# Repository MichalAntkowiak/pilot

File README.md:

# Pilot IR na ATtiny1614

Pilot na podczerwień do telewizora, zaprojektowany od zera w KiCadzie: od policzenia wartości elementów, przez schemat, po samodzielnie poprowadzoną dwuwarstwową płytkę drukowaną. Zasilany z dwóch baterii AAA, ma sześć przycisków i diodę IR sterowaną przez tranzystor.

**Status:** projekt PCB ukończony (ERC, DRC i zgodność ze schematem bez błędów), firmware w przygotowaniu.

## Założenia projektu

**Pilot nadający.** Kody komend telewizora są zapisane w firmware, a naciśnięcie przycisku wysyła gotową komendę. Wariant „uczący się”, z odbiornikiem IR do nagrywania oryginalnego pilota, zostawiłem na wersję drugą. Tor nadawczy jest w obu wersjach identyczny, więc najpierw warto go opanować.

**Zasilanie z 2 × AAA, bez włącznika.** ATtiny1614 pracuje bezpośrednio z baterii (od 1,8 V), a w uśpieniu pobiera ułamek mikroampera, więc wyłącznik nie jest potrzebny. Mikrokontroler budzi naciśnięcie przycisku.

**Mikrokontroler dobrany pod baterie.** Rozważałem znany mi już ESP32-C3, ale potrzebuje on stabilizowanych 3,3 V (dwie baterie AAA dają 3 V i mniej) i pobiera znacznie więcej prądu. Wymagałby przetwornicy na płytce i szybciej rozładowywałby baterie. ATtiny upraszcza schemat kosztem nowego toolchainu: megaTinyCore w Arduino IDE i programowanie przez UPDI.

**Sześć przycisków:** zasilanie, głośność +/−, kanał +/− i wyciszenie.

**Nośna 38 kHz generowana sprzętowo** przez timer TCA0 na pinie PB0, więc jej przebieg nie zależy od tego, co w danej chwili robi program.

## Schemat

Schemat składa się z czterech bloków.

**Zasilanie.** Koszyk BT1 zasila sieć VCC, a kondensator C1 (100 nF) odsprzęga ATtiny.

**Przyciski.** Każdy zwiera swój pin do masy. Rezystory podciągające są wbudowane w ATtiny i włączane programowo, więc na płytce ich nie ma. Połączenia prowadzą etykiety sieci, dzięki czemu schemat pozostaje czytelny.

**Tor nadawczy.** Pin PB0 (etykieta `IR_OUT`) przez R1 steruje bazą tranzystora Q1, który przełącza obwód VCC → R2 → D1 → Q1 → GND. Kondensator C2 (22 µF) przy diodzie pokrywa impulsy prądu.

**Programowanie.** Złącze J1 wyprowadza UPDI (PA0), VCC i GND.

## Obliczenia

Wartości elementów toru nadawczego policzyłem sam, a potem dobrałem najbliższe wartości z typoszeregu.

**R2: ograniczenie prądu diody IR (cel: 100 mA)**

```
R2 = (U_bat − U_D − U_CE(sat)) / I_D
   = (3,0 V − 1,3 V − 0,3 V) / 0,1 A = 14 Ω   →   15 Ω  (I_D ≈ 93 mA)
```

Zaokrąglenie w górę: nieco mniejszy prąd, więc założenie nie zostaje przekroczone.

**R1: rezystor bazy Q1**

```
I_B ≈ I_C / 10 = 93 mA / 10 = 9,3 mA
R1  = (U_PB0 − U_BE) / I_B = (3,0 V − 0,8 V) / 9,3 mA ≈ 236,6 Ω   →   220 Ω  (I_B ≈ 10 mA)
```

Zaokrąglenie w dół: większy prąd bazy daje pewniejsze nasycenie tranzystora.

**C2: zbiornik na impulsy diody**

```
C = I · t / ΔV = 0,093 A · 9 µs / 0,1 V ≈ 8,4 µF   →   22 µF
```

t to czas jednego błysku przy nośnej 38 kHz, a ΔV to dopuszczalny spadek napięcia. Najbliższa wartość to 10 µF, ale ceramiczne kondensatory tracą pojemność pod napięciem i 10 µF przy 3 V realnie ma około 7 µF. Stąd 22 µF w obudowie 1206.

## Komponenty

| Oznaczenie | Element | Obudowa | Rola |
|---|---|---|---|
| U1 | ATtiny1614 | SOIC-14 | mikrokontroler |
| D1 | dioda IR 940 nm | 5 mm, montaż poziomy | nadajnik podczerwieni |
| Q1 | tranzystor NPN 2N3904 | TO-92 | przełącznik diody |
| R1 | rezystor 220 Ω | 0805 | rezystor bazy Q1 |
| R2 | rezystor 15 Ω | 0805 | ograniczenie prądu diody |
| C1 | kondensator ceramiczny 100 nF | 0805 | odsprzęganie U1 |
| C2 | kondensator ceramiczny 22 µF | 1206 | zbiornik na impulsy diody |
| SW1–SW6 | przycisk tact switch | 6 × 6 mm, THT | przyciski pilota |
| BT1 | koszyk 2 × AAA | Keystone 2468 | zasilanie, spód płytki |
| J1 | listwa goldpin 1 × 3 | raster 2,54 mm | programowanie UPDI |

## Przypisanie pinów

| Pin ATtiny1614 | Sieć | Funkcja |
|---|---|---|
| PA0 (10) | UPDI | programowanie |
| PA1 (11) | power | włącz / wyłącz |
| PA2 (12) | vol+ | głośniej |
| PA3 (13) | vol− | ciszej |
| PA4 (2) | ch+ | następny kanał |
| PA5 (3) | ch− | poprzedni kanał |
| PA6 (4) | mute | wyciszenie |
| PB0 (9) | IR_OUT | nośna 38 kHz do tranzystora |
| PA7, PB1–PB3 | – | niepodłączone |

## Płytka

Płytka jest dwuwarstwowa. Najważniejsze decyzje przy rozmieszczeniu:

- **Dioda IR przy górnej krawędzi**, w wersji poziomej, soczewką do przodu. Celuje w telewizor, a nie w sufit. Footprint trzyma ją 3 mm nad laminatem, więc krawędź płytki nie zasłania światła.
- **Tor nadawczy (C2, R2, D1, Q1) ciasno pod diodą.** Przez tę pętlę płyną impulsy 93 mA, więc im jest mniejsza, tym mniej zakłóceń. Ścieżki w tym torze mają szerokość 0,5 mm.
- **C1 tuż przy pinach zasilania U1** (piny 1 i 14).
- **Koszyk baterii na spodzie, poniżej przycisków**, a nie pod nimi. Nóżki przycisków THT wystają na spód i uchwyt by na nie naciskał.
- **Wylewka masy na całej warstwie B.Cu**, do której podłączone są wszystkie pola GND.

Weryfikacja: ERC bez błędów, DRC bez naruszeń i niepołączonych elementów, zgodność PCB ze schematem bez różnic.

*Zielona dioda na renderach to domyślny model 3D z biblioteki KiCada. Prawdziwa dioda IR jest przezroczysta, a jej światło widać dopiero w kamerze telefonu.*

## Czego się nauczyłem

**Liczenie zamiast przepisywania.** Wartości R1, R2 i C2 policzyłem sam z prawa Ohma i ze wzoru C = I·t/ΔV. Nauczyłem się też, że kierunek zaokrąglenia do typoszeregu zależy od tego, która strona jest bezpieczna: R2 w górę, R1 w dół, a C2 w górę z zapasem na utratę pojemności ceramiki pod napięciem.

**Tranzystor jako przełącznik.** Pin mikrokontrolera nie da prądu, jakiego dioda IR potrzebuje na dobry zasięg, więc steruje tranzystorem, który przełącza diodę. Prąd bazy równy około 1/10 prądu kolektora zapewnia pełne nasycenie.

**Dwa różne zadania kondensatorów.** 100 nF przy mikrokontrolerze tłumi krótkie szpilki prądu logiki cyfrowej, a 22 µF przy diodzie pokrywa jej impulsy. Na schemacie położenie kondensatora nie ma znaczenia, na płytce decyduje o tym, czy w ogóle spełnia swoje zadanie.

**Czytelny schemat.** Etykiety sieci zamiast plątaniny przewodów, flagi PWR_FLAG na sieciach zasilania i flagi „niepodłączony” na wolnych pinach, a na koniec ERC doprowadzony do zera.

**Rozmieszczenie przed trasowaniem.** Krzyżujące się linie połączeń to sygnał, żeby przestawić elementy, a nie kombinować ze ścieżkami. Zamiana stronami tranzystora i pary R2/C2 usunęła jedyne krzyżowanie w torze diody.

**Pierwsze samodzielne trasowanie.** Szersze ścieżki tam, gdzie płynie większy prąd, przelotki do zmiany warstwy (pola SMD istnieją tylko na wierzchu płytki), wylewka masy i DRC doprowadzony do zera razem z testem zgodności ze schematem.

**Mechanika to też część projektu.** Kierunek świecenia diody, właściwy rozmiar koszyka baterii (AA i AAA to zupełnie inne footprinty) i to, co wystaje na spód płytki, trzeba sprawdzić, zanim płytka trafi do produkcji.

## Dalsze kroki

- **Firmware:** Arduino IDE z megaTinyCore, wysyłanie kodów w protokole telewizora, uśpienie mikrokontrolera i budzenie przyciskiem.
- **Wersja 2:** odbiornik IR, czyli pilot uczący się, który nagrywa sygnał z oryginalnego pilota.
- **Produkcja:** porządki na sitodruku i zamówienie płytki.

## Pliki projektu

| Plik | Zawartość |
|---|---|
| `pilot.kicad_pro` | projekt KiCad |
| `pilot.kicad_sch` | schemat |
| `pilot.kicad_pcb` | płytka drukowana |
| `images/` | rendery 3D i schemat |

Projekt wykonany w KiCad 10.0.5.

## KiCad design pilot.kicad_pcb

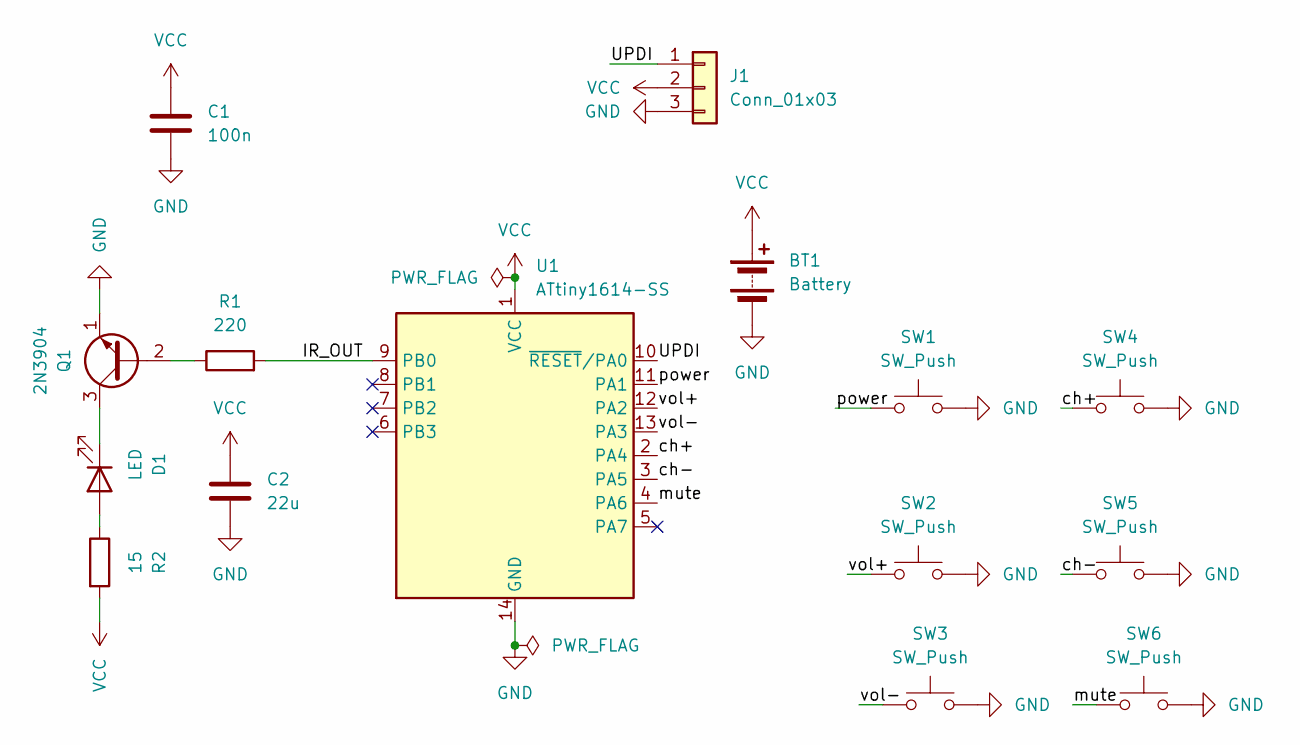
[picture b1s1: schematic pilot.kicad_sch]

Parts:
BT1: Battery; BatteryHolder_Keystone_2468_2xAAA
C1: 100n; C_0805_2012Metric
C2: 22u; C_1206_3216Metric
D1: LED; LED_D5.0mm_Horizontal_O1.27mm_Z3.0mm
J1: Conn_01x03; PinHeader_1x03_P2.54mm_Vertical
Q1: 2N3904; TO-92_Inline
R1: 220; R_0805_2012Metric
R2: 15; R_0805_2012Metric
SW1, SW2, SW3, SW4, SW5, SW6: SW_Push; SW_PUSH_6mm
U1: ATtiny1614-SS; SOIC-14_3.9x8.7mm_P1.27mm

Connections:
/IR_OUT: R1.2, U1.9 (PB0)
/UPDI: J1.1, U1.10 (~RESET/PA0)
/ch+: SW4.1, U1.2 (PA4)
/ch-: SW5.1, U1.3 (PA5)
/mute: SW6.1, U1.4 (PA6)
/power: SW1.1, U1.11 (PA1)
/vol+: SW2.1, U1.12 (PA2)
/vol-: SW3.1, U1.13 (PA3)
GND: BT1.2 (-), C1.2, C2.2, J1.3, Q1.1 (E), SW1.2, SW2.2, SW3.2, SW4.2, SW5.2, SW6.2, U1.14 (GND)
unnamed: D1.2 (A), R2.1
unnamed: D1.1 (K), Q1.3 (C)
unnamed: Q1.2 (B), R1.1
VCC: BT1.1 (+), C1.1, C2.1, J1.2, R2.2, U1.1 (VCC)

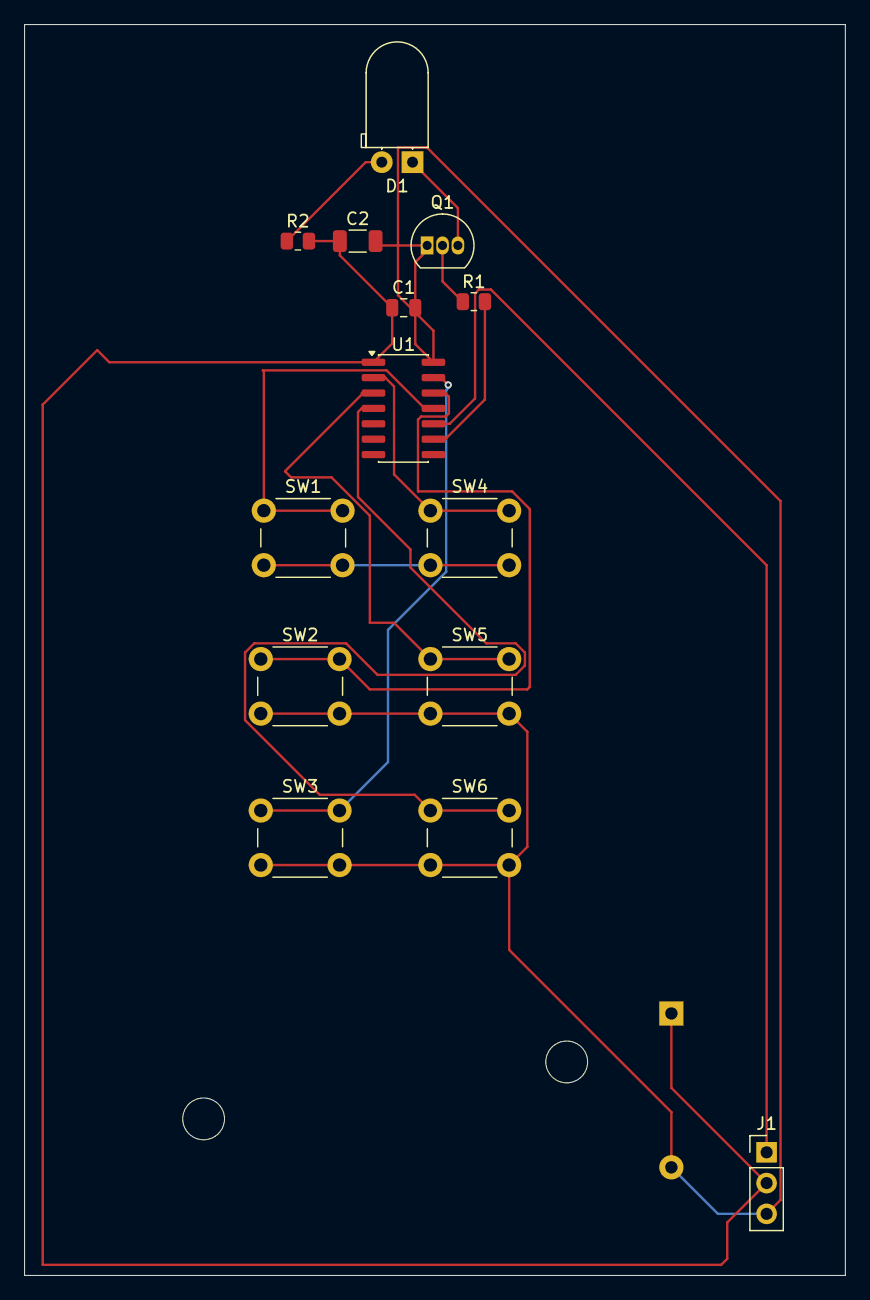
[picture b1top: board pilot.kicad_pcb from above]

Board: 2 copper layers, 67.8 x 103.2 mm, 15 parts (1 on the bottom side), 13 nets.
